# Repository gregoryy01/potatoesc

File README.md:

# potatoesc
This repo contains greg's attempt to make a bldc controller for Semar Urban, please be nice

notes from almighty bimo:
BIG capacitance
bootstrap capacitance specs
calculate gate resistance

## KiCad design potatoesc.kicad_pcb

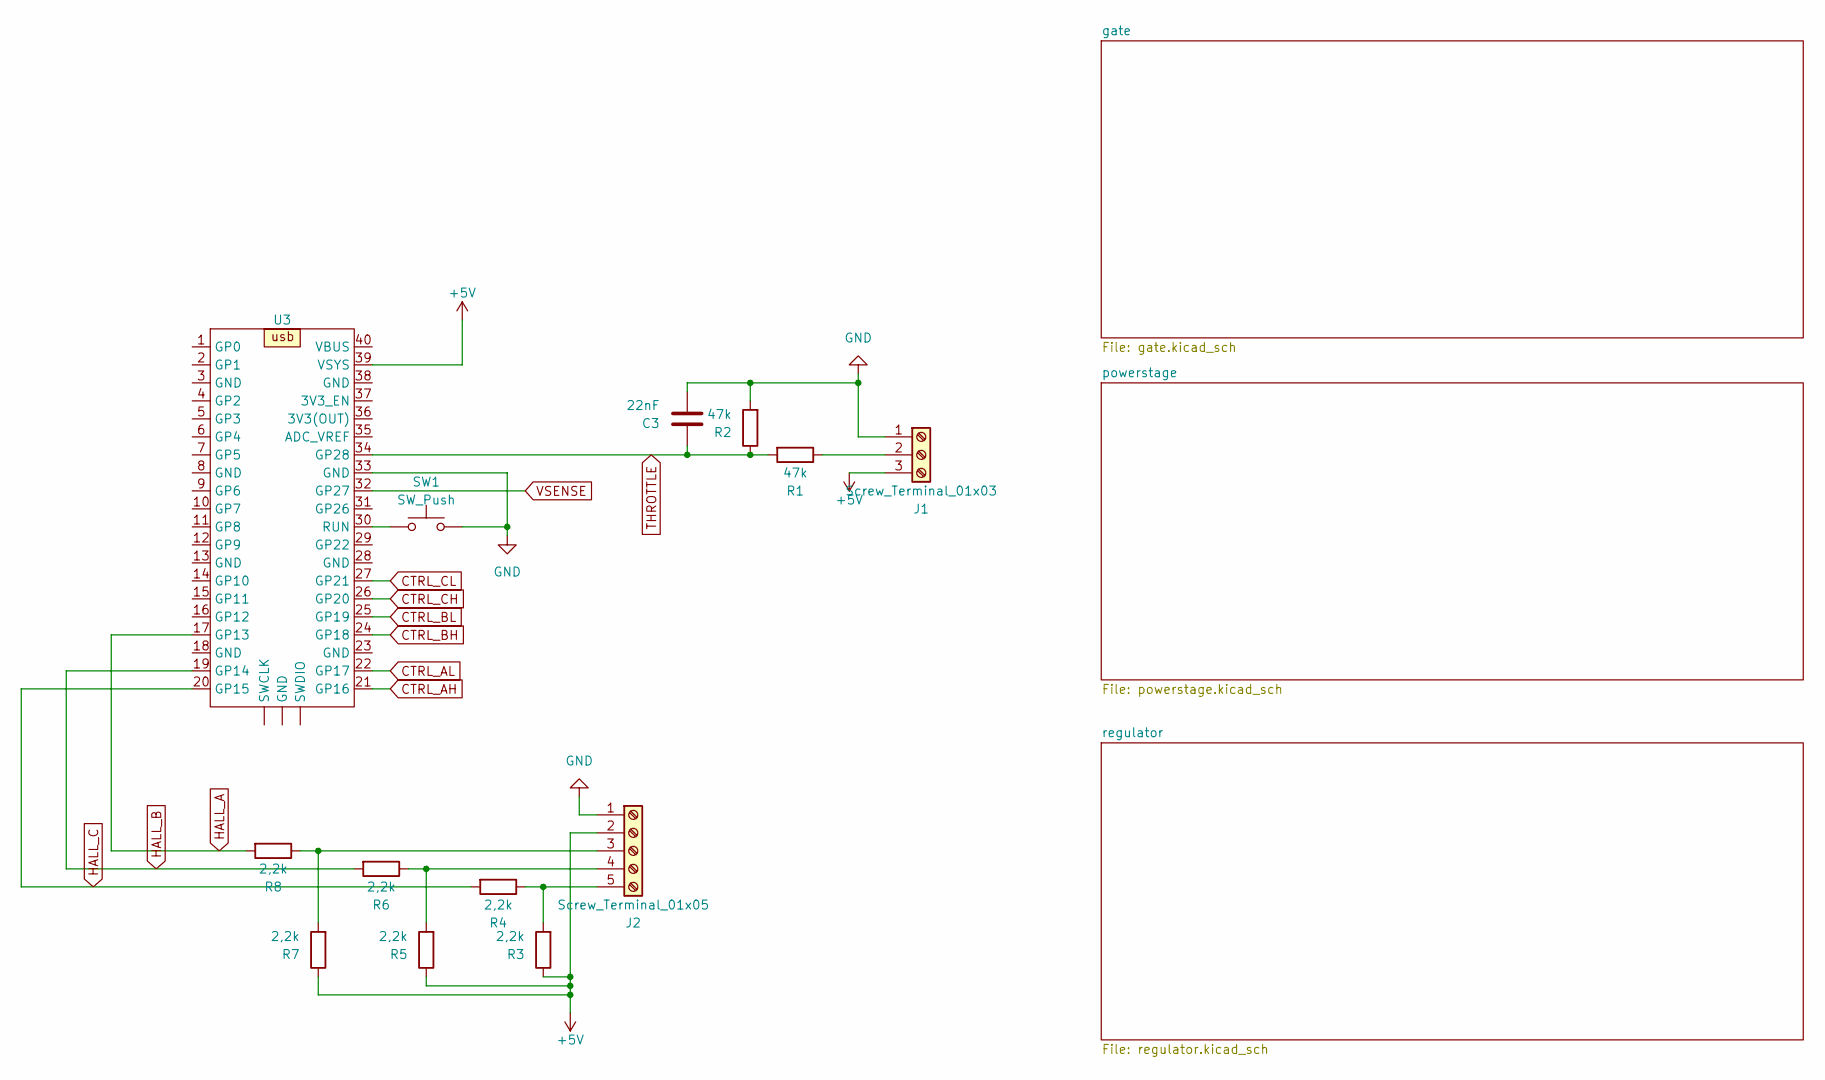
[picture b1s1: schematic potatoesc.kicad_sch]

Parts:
C3: 22nF; C_0805_2012Metric_Pad1.18x1.45mm_HandSolder
J1: Screw_Terminal_01x03; TerminalBlock_Phoenix_MKDS-1,5-3-5.08_1x03_P5.08mm_Horizont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
J2: Screw_Terminal_01x05; TerminalBlock_Phoenix_MKDS-1,5-5-5.08_1x05_P5.08mm_Horizont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
R1, R2: 47k; R_1206_3216Metric_Pad1.30x1.75mm_HandSolder
R3, R4, R5, R6, R7, R8: 2,2k; R_1206_3216Metric_Pad1.30x1.75mm_HandSolder
SW1: SW_Push; SW_PUSH_6mm
U3: RPi_Pico_SMD_TH

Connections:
+5V: J1.3, J2.2, R3.1, R5.1, R7.1, U3.39 (VSYS); also elsewhere on the board
CTRL_AH: U3.21 (GP16); also elsewhere on the board
CTRL_AL: U3.22 (GP17); also elsewhere on the board
CTRL_BH: U3.24 (GP18); also elsewhere on the board
CTRL_BL: U3.25 (GP19); also elsewhere on the board
CTRL_CH: U3.26 (GP20); also elsewhere on the board
CTRL_CL: U3.27 (GP21); also elsewhere on the board
GND: C3.2, J1.1, J2.1, R2.2, SW1.2, U3.33 (GND); also elsewhere on the board
HALL_A: R8.2, U3.17 (GP13)
HALL_B: R6.2, U3.19 (GP14)
HALL_C: R4.2, U3.20 (GP15)
unnamed: J1.2, R1.1
unnamed: J2.3, R7.2, R8.1
unnamed: J2.4, R5.2, R6.1
unnamed: J2.5, R3.2, R4.1
unnamed: SW1.1, U3.30 (RUN)
THROTTLE: C3.1, R1.2, R2.1, U3.34 (GP28)
VSENSE: U3.32 (GP27); also elsewhere on the board

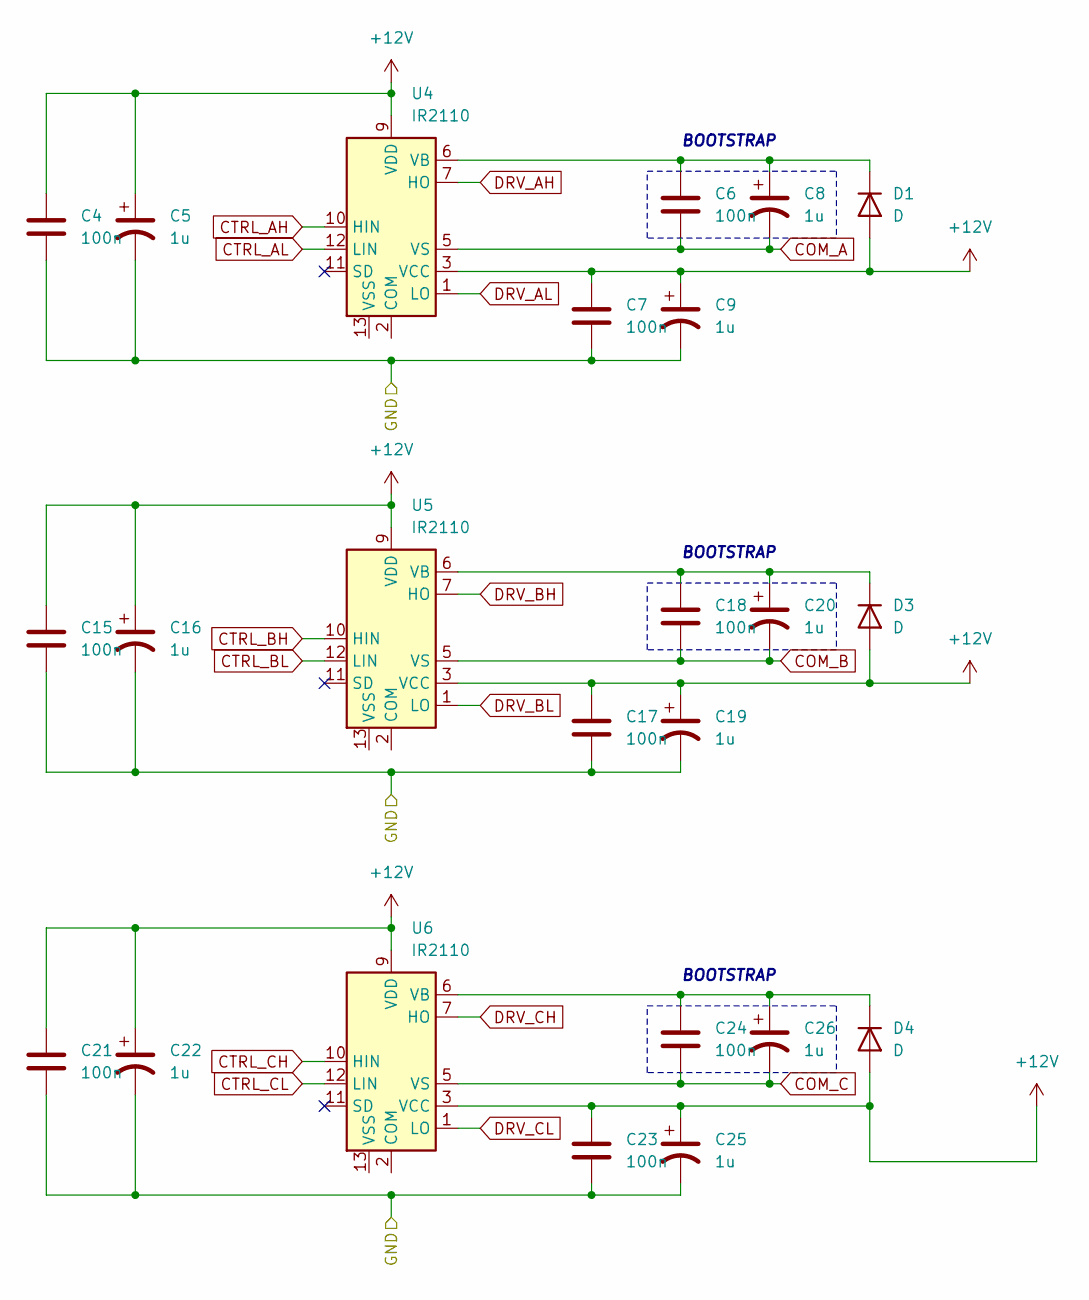
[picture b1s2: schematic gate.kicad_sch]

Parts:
C4, C6, C7, C15, C17, C18, C21, C23, C24: 100n; C_0805_2012Metric_Pad1.18x1.45mm_HandSolder
C5, C8, C9, C16, C19, C20, C22, C25, C26: 1u; CP_Elec_5x4.4
D1, D3, D4: D; D_SMA_Handsoldering
U4, U5, U6: IR2110; DIP-14_W7.62mm_Socket_LongPads

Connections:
+12V: C4.1, C5.1, C7.1, C9.1, C15.1, C16.1, C17.1, C19.1, C21.1, C22.1, C23.1, C25.1, D1.2 (A), D3.2 (A), D4.2 (A), U4.3 (VCC), U4.9 (VDD), U5.3 (VCC), U5.9 (VDD), U6.3 (VCC), U6.9 (VDD); also elsewhere on the board
/gate/GND: C4.2, C5.2, C7.2, C9.2, C15.2, C16.2, C17.2, C19.2, C21.2, C22.2, C23.2, C25.2
COM_A: C6.2, C8.2, U4.5 (VS); also elsewhere on the board
COM_B: C18.2, C20.2, U5.5 (VS); also elsewhere on the board
COM_C: C24.2, C26.2, U6.5 (VS); also elsewhere on the board
CTRL_AH: U4.10 (HIN); also elsewhere on the board
CTRL_AL: U4.12 (LIN); also elsewhere on the board
CTRL_BH: U5.10 (HIN); also elsewhere on the board
CTRL_BL: U5.12 (LIN); also elsewhere on the board
CTRL_CH: U6.10 (HIN); also elsewhere on the board
CTRL_CL: U6.12 (LIN); also elsewhere on the board
DRV_AH: U4.7 (HO); also elsewhere on the board
DRV_AL: U4.1 (LO); also elsewhere on the board
DRV_BH: U5.7 (HO); also elsewhere on the board
DRV_BL: U5.1 (LO); also elsewhere on the board
DRV_CH: U6.7 (HO); also elsewhere on the board
DRV_CL: U6.1 (LO); also elsewhere on the board
unnamed: C6.1, C8.1, D1.1 (K), U4.6 (VB)
unnamed: C18.1, C20.1, D3.1 (K), U5.6 (VB)
unnamed: C24.1, C26.1, D4.1 (K), U6.6 (VB)

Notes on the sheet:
BOOTSTRAP

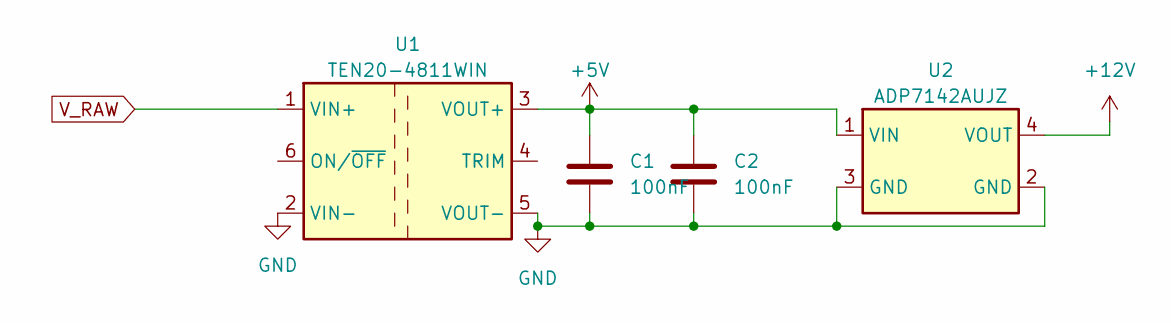
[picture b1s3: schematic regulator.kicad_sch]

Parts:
C1, C2: 100nF; C_0805_2012Metric_Pad1.18x1.45mm_HandSolder
U1: TEN20-4811WIN; Converter_DCDC_TRACO_TEN20-xxxx_THT
U2: ADP7142AUJZ; MT3608_module

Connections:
+5V: C1.2, C2.2, U1.3 (VOUT+), U2.1 (VIN); also elsewhere on the board
+12V: U2.4 (VOUT); also elsewhere on the board
GND: C1.1, C2.1, U1.2 (VIN-), U1.5 (VOUT-), U2.2 (GND), U2.3 (GND); also elsewhere on the board
V_RAW: U1.1 (VIN+); also elsewhere on the board

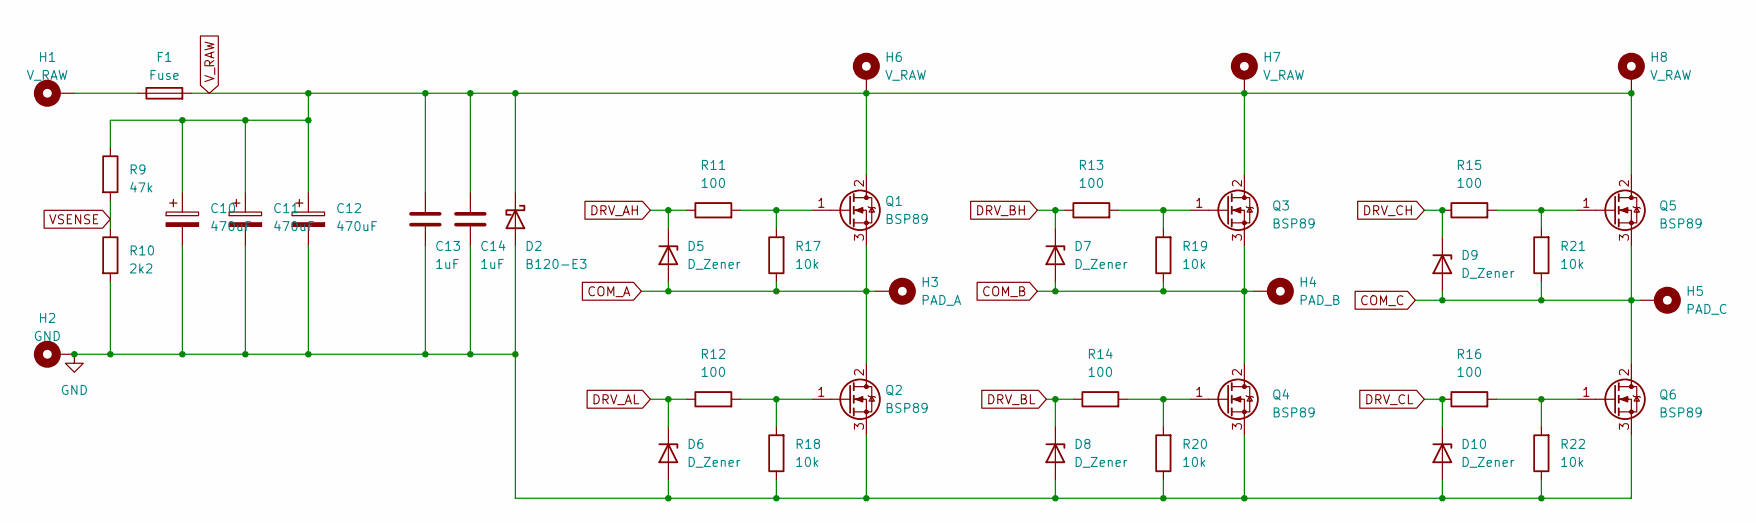
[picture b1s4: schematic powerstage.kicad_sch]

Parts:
C10, C11, C12: 470uF; CP_Radial_D17.0mm_P7.50mm
C13, C14: 1uF; C_0805_2012Metric_Pad1.18x1.45mm_HandSolder
D2: B120-E3; D_A-405_P10.16mm_Horizontal
D5, D6, D7, D8, D9, D10: D_Zener; D_5W_P12.70mm_Horizontal
F1: Fuse; Fuse_Blade_ATO_directSolder
H1, H6, H7, H8: V_RAW; SolderWirePad_1x01_SMD_5x10mm
H2: GND; SolderWirePad_1x01_SMD_5x10mm
H3: PAD_A; SolderWirePad_1x01_SMD_5x10mm
H4: PAD_B; SolderWirePad_1x01_SMD_5x10mm
H5: PAD_C; SolderWirePad_1x01_SMD_5x10mm
Q1, Q2, Q3, Q4, Q5, Q6: BSP89; TO-220-3_Horizontal_TabDown
R9: 47k; R_1206_3216Metric_Pad1.30x1.75mm_HandSolder
R10: 2k2; R_1206_3216Metric_Pad1.30x1.75mm_HandSolder
R11, R12, R13, R14, R15, R16: 100; R_1206_3216Metric_Pad1.30x1.75mm_HandSolder
R17, R18, R19, R20, R21, R22: 10k; R_1206_3216Metric_Pad1.30x1.75mm_HandSolder

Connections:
COM_A: D5.2 (A), H3.1, Q1.3 (S), Q2.2 (D), R17.1; also elsewhere on the board
COM_B: D7.2 (A), H4.1, Q3.3 (S), Q4.2 (D), R19.1; also elsewhere on the board
COM_C: D9.2 (A), H5.1, Q5.3 (S), Q6.2 (D), R21.1; also elsewhere on the board
DRV_AH: D5.1 (K), R11.1; also elsewhere on the board
DRV_AL: D6.1 (K), R12.1; also elsewhere on the board
DRV_BH: D7.1 (K), R13.1; also elsewhere on the board
DRV_BL: D8.1 (K), R14.1; also elsewhere on the board
DRV_CH: D9.1 (K), R15.1; also elsewhere on the board
DRV_CL: D10.1 (K), R16.1; also elsewhere on the board
GND: C10.2, C11.2, C12.2, C13.2, C14.2, D2.2 (A), D6.2 (A), D8.2 (A), D10.2 (A), H2.1, Q2.3 (S), Q4.3 (S), Q6.3 (S), R10.2, R18.1, R20.1, R22.1; also elsewhere on the board
unnamed: F1.1, H1.1
unnamed: Q1.1 (G), R11.2, R17.2
unnamed: Q2.1 (G), R12.2, R18.2
unnamed: Q3.1 (G), R13.2, R19.2
unnamed: Q4.1 (G), R14.2, R20.2
unnamed: Q5.1 (G), R15.2, R21.2
unnamed: Q6.1 (G), R16.2, R22.2
VSENSE: R9.2, R10.1; also elsewhere on the board
V_RAW: C10.1, C11.1, C12.1, C13.1, C14.1, D2.1 (K), F1.2, H6.1, H7.1, H8.1, Q1.2 (D), Q3.2 (D), Q5.2 (D), R9.1; also elsewhere on the board

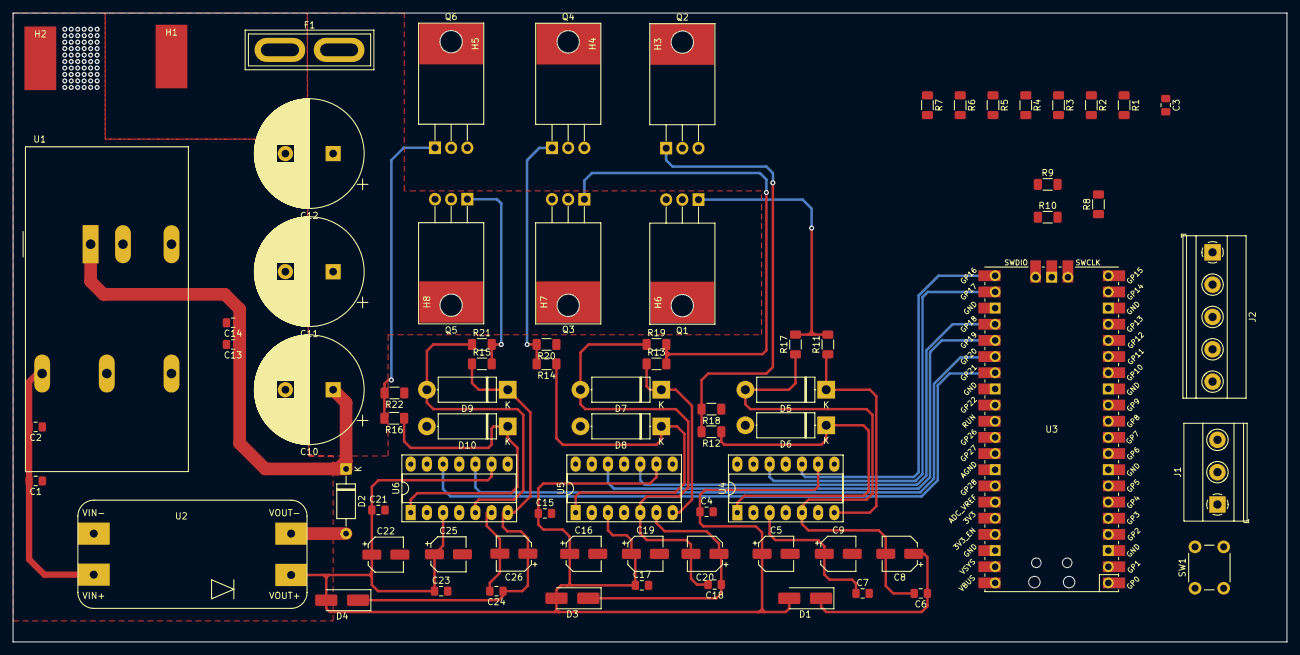
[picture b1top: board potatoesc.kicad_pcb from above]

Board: 2 copper layers, 200.2 x 98.8 mm, 82 parts (0 on the bottom side), 40 nets.

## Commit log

2024-06-23 Added Base Kicad File
2024-06-23 Added MCU and regulators
2024-06-24 Added advice
2024-06-24 Added driver and powerstage
2024-06-24 initial pcb placment, some components needs to be replaced by smd
2024-06-25 Added first pcb design
